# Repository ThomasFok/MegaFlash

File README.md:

# MegaFlash for Apple IIc/IIc+

MegaFlash is an internal storage device for Apple IIc/IIc plus computer.

## Feature List

- 128MB/256MB Capacity, divided into 4/8 ProDOS Drives
- 400kB RAM Disk
- ROM Disk for Disaster Recovery
- 256kB Slinky Emulation on stock firmware
- Boot Menu (Similar to ROM4X/5X)
- Control Panel
- Real Time Clock with ProDOS clock driver
- Network Time Sync (NTP Client)
- Upload/Download ProDOS Image file via WIFI and TFTP Server
- Upload/Download ProDOS Image file via XModem and USB serial port
- FPU for Applesoft BASIC
- Bug fixes of System ROM and Applesoft

A brief [user guide](/userguide.pdf) is available for more information.

## Requirement
- Apple IIc computer with Memory Expansion Card connector or
- Apple IIc plus computer

System ROM replacement is required for MegaFlash to function.

## Hardware
The hardware is quite simple.  All the heavy work is handled by Pi Pico.  Apple 65C02 CPU only needs to copy data between RAM and Pico. Schematic is available [here](./kicad/rev1.0a/schematic-rev1.0a.pdf).

- Raspberry Pi Pico2 W
- Winbond 25Q01 NOR Flash memory
- GAL16V8 PLD for address decode
- 5V to 3.3V Logic Level Shifter

## Project Directories

There are 3 software projects. There is not enough space in Apple ROM to store the Control Panel program.  The program is stored in Pico flash memory. 

`firmware` Project Directory of Apple ROM Patches\
`cpanel` Control Panel project\
`pico` Raspberry Pi Pico firmware\
`common` Common header files used by all 3 projects

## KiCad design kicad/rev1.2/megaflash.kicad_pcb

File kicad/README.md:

# MegaFlash PCB

Currently, there are three PCB revisions, 1.0A, 1.1B and 1.2. They are functionally identical. 

Rev 1.0A board is more compact. It is optimized for machine assembly. 

Rev 1.1B board is bigger. It is designed for hand assembly.  The components are either through hole or 1.27mm pitch SOICs. The picture below is Rev 1.1A PCB. The positions of the flash chips and mounting hole are slightly different on Rev 1.1B PCB.

Rev 1.2 board replaces the GAL16V8 PLD with three 74HC138.

A brief [PCB Assembly Notes](./pcbassemblynotes.pdf) is available for more information.

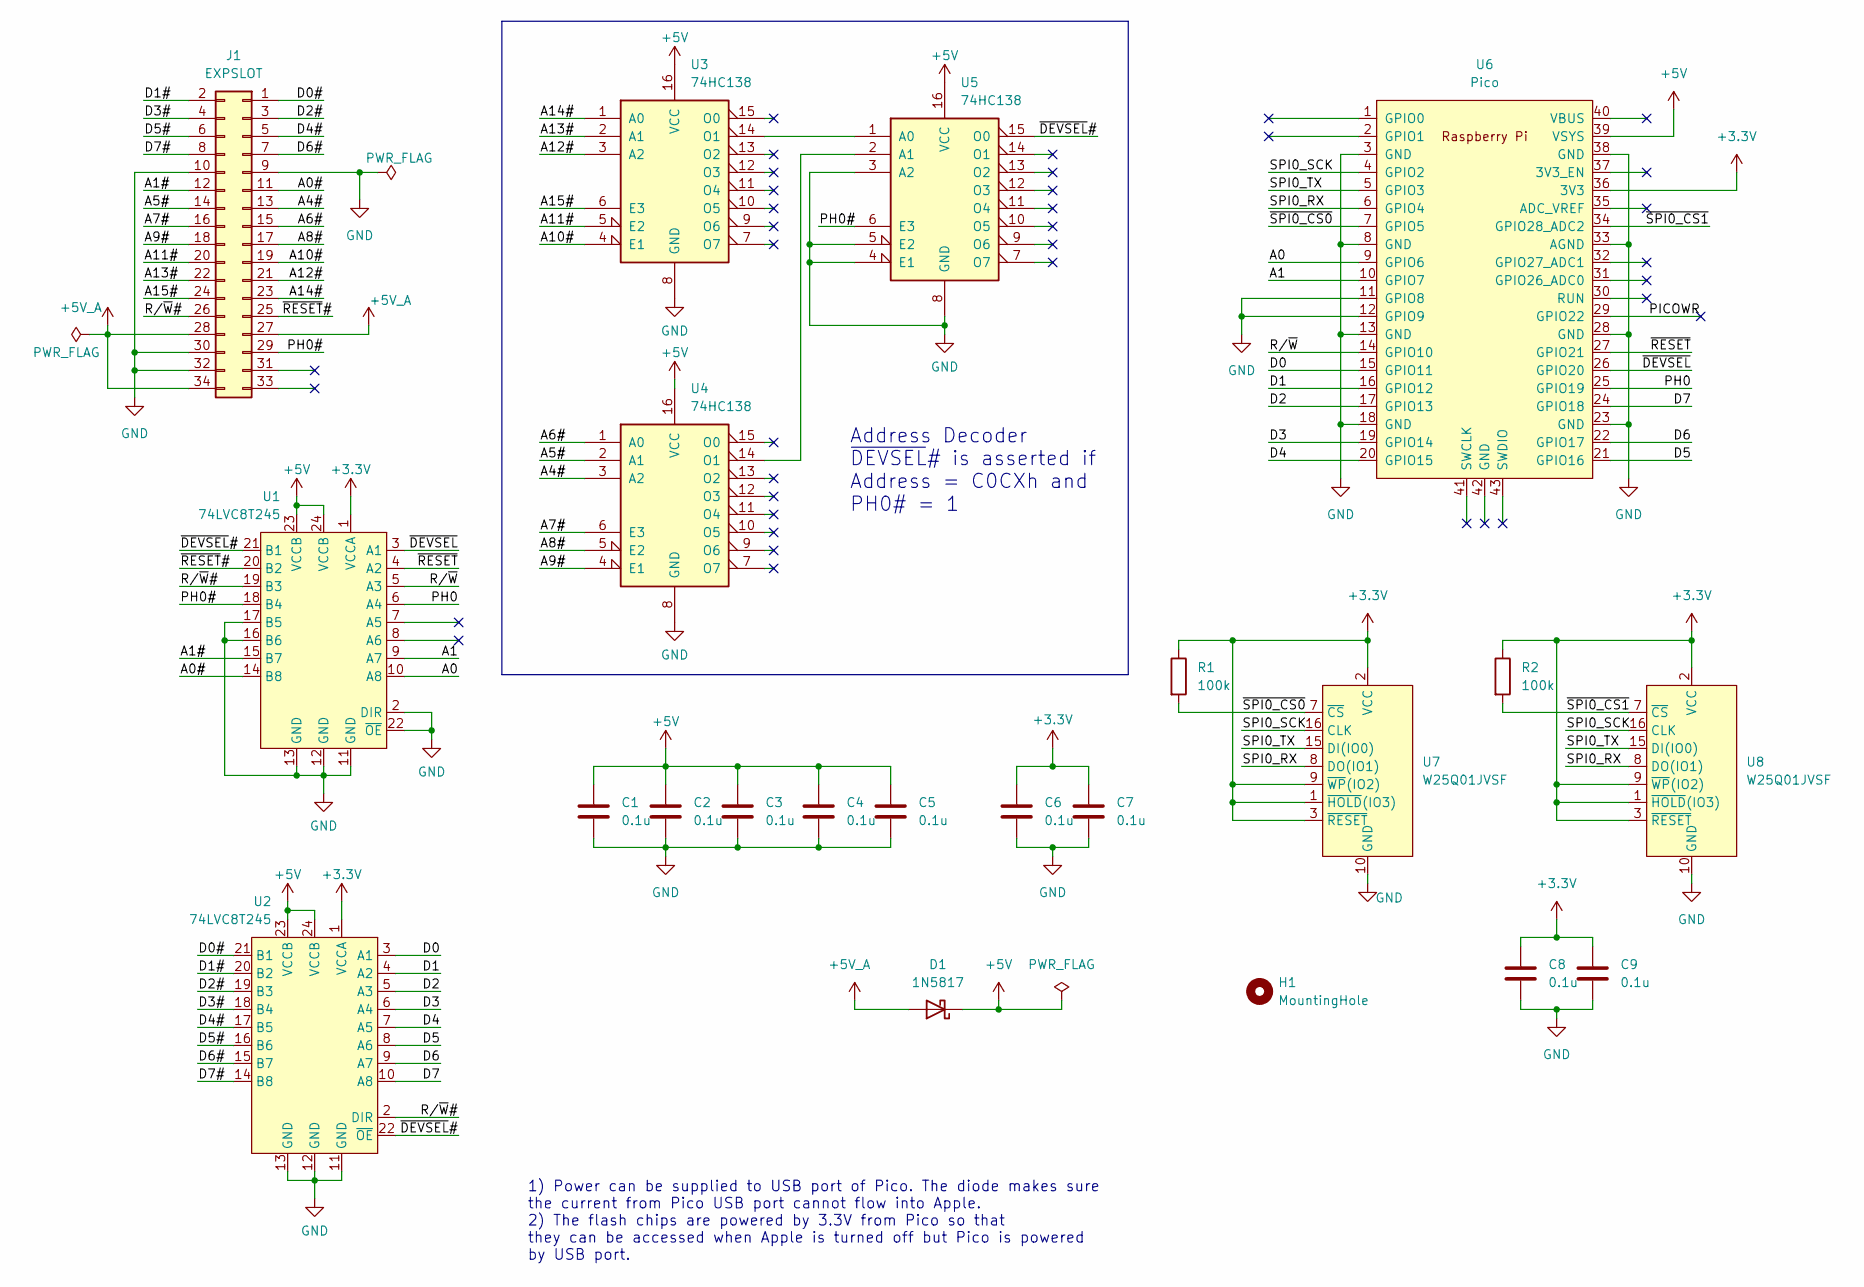
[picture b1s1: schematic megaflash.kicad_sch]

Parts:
C1, C2, C3, C4, C5, C6, C7, C8, C9: 0.1u; C_Disc_D5.1mm_W3.2mm_P5.00mm; Mouser Part No 594-K104K15X7RF5WH5
D1: 1N5817; D_DO-41_SOD81_P10.16mm_Horizontal; Mouser Part No 625-1N5817-E3/53
H1: MountingHole; MountingHole_2.7mm_M2.5
J1: EXPSLOT; PinHeader_2x17_P2.54mm_Vertical_Mirror; Mouser Part No 200-TSW11715GD
R1, R2: 100k; R_Axial_DIN0207_L6.3mm_D2.5mm_P10.16mm_Horizontal
U1, U2: 74LVC8T245; SOIC-24W_7.5x15.4mm_P1.27mm; Mfr Part No SN74LVC8T245DWR; Mouser Part No 595-SN74LVC8T245DWR
U3, U4, U5: 74HC138; SOIC-16_3.9x9.9mm_P1.27mm; Mouser Part No 595-SN74HC138QDRG4Q1
U6: Pico; RPi_Pico_SMD_NO_LABEL_NO_DEBUG
U7, U8: W25Q01JVSF; SOIC-16W_7.5x10.3mm_P1.27mm; Mouser Part No 454-W25Q01JVSFIM

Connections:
+3.3V: C6.1, C7.1, C8.1, C9.1, R1.1, R2.1, U1.1 (VCCA), U2.1 (VCCA), U6.36 (3V3), U7.1 (~HOLD(IO3)), U7.2 (VCC), U7.3 (~RESET), U7.9 (~WP(IO2)), U8.1 (~HOLD(IO3)), U8.2 (VCC), U8.3 (~RESET), U8.9 (~WP(IO2))
+5V: C1.1, C2.1, C3.1, C4.1, C5.1, D1.1 (K), U1.23 (VCCB), U1.24 (VCCB), U2.23 (VCCB), U2.24 (VCCB), U3.16 (VCC), U4.16 (VCC), U5.16 (VCC), U6.39 (VSYS)
+5V_A: D1.2 (A), J1.27, J1.28, J1.34
/A0: U1.10 (A8), U6.9 (GPIO6)
/A0#: J1.11, U1.14 (B8)
/A1: U1.9 (A7), U6.10 (GPIO7)
/A1#: J1.12, U1.15 (B7)
/A4#: J1.13, U4.3 (A2)
/A5#: J1.14, U4.2 (A1)
/A6#: J1.15, U4.1 (A0)
/A7#: J1.16, U4.6 (E3)
/A8#: J1.17, U4.5 (E2)
/A9#: J1.18, U4.4 (E1)
/A10#: J1.19, U3.4 (E1)
/A11#: J1.20, U3.5 (E2)
/A12#: J1.21, U3.3 (A2)
/A13#: J1.22, U3.2 (A1)
/A14#: J1.23, U3.1 (A0)
/A15#: J1.24, U3.6 (E3)
/D0: U2.3 (A1), U6.15 (GPIO11)
/D0#: J1.1, U2.21 (B1)
/D1: U2.4 (A2), U6.16 (GPIO12)
/D1#: J1.2, U2.20 (B2)
/D2: U2.5 (A3), U6.17 (GPIO13)
/D2#: J1.3, U2.19 (B3)
/D3: U2.6 (A4), U6.19 (GPIO14)
/D3#: J1.4, U2.18 (B4)
/D4: U2.7 (A5), U6.20 (GPIO15)
/D4#: J1.5, U2.17 (B5)
/D5: U2.8 (A6), U6.21 (GPIO16)
/D5#: J1.6, U2.16 (B6)
/D6: U2.9 (A7), U6.22 (GPIO17)
/D6#: J1.7, U2.15 (B7)
/D7: U2.10 (A8), U6.24 (GPIO18)
/D7#: J1.8, U2.14 (B8)
/PH0: U1.6 (A4), U6.25 (GPIO19)
/PH0#: J1.29, U1.18 (B4), U5.6 (E3)
/PICOWR: U6.29 (GPIO22)
/R/~W: U1.5 (A3), U6.14 (GPIO10)
/R/~W#: J1.26, U1.19 (B3), U2.2 (DIR)
/SPI0_RX: U6.6 (GPIO4), U7.8 (DO(IO1)), U8.8 (DO(IO1))
/SPI0_SCK: U6.4 (GPIO2), U7.16 (CLK), U8.16 (CLK)
/SPI0_TX: U6.5 (GPIO3), U7.15 (DI(IO0)), U8.15 (DI(IO0))
/~DEVSEL: U1.3 (A1), U6.26 (GPIO20)
/~DEVSEL#: U1.21 (B1), U2.22 (~OE), U5.15 (O0)
/~RESET: U1.4 (A2), U6.27 (GPIO21)
/~RESET#: J1.25, U1.20 (B2)
/~SPI0_CS0: R1.2, U6.7 (GPIO5), U7.7 (~CS)
/~SPI0_CS1: R2.2, U6.34 (GPIO28_ADC2), U8.7 (~CS)
GND: C1.2, C2.2, C3.2, C4.2, C5.2, C6.2, C7.2, C8.2, C9.2, J1.9, J1.10, J1.30, J1.32, U1.2 (DIR), U1.11 (GND), U1.12 (GND), U1.13 (GND), U1.16 (B6), U1.17 (B5), U1.22 (~OE), U2.11 (GND), U2.12 (GND), U2.13 (GND), U3.8 (GND), U4.8 (GND), U5.3 (A2), U5.4 (E1), U5.5 (E2), U5.8 (GND), U6.3 (GND), U6.8 (GND), U6.11 (GPIO8), U6.12 (GPIO9), U6.13 (GND), U6.18 (GND), U6.23 (GND), U6.28 (GND), U6.33 (AGND), U6.38 (GND), U7.10 (GND), U8.10 (GND)
unnamed: U3.14 (O1), U5.1 (A0)
unnamed: U4.14 (O1), U5.2 (A1)

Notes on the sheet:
Address Decoder ~{DEVSEL}# is asserted if Address = C0CXh and PH0# = 1
1) Power can be supplied to USB port of Pico. The diode makes sure the current from Pico USB port cannot flow into Apple. 2) The flash chips are powered by 3.3V from Pico so that they can be accessed when Apple is turned off but Pico is powered by USB port.

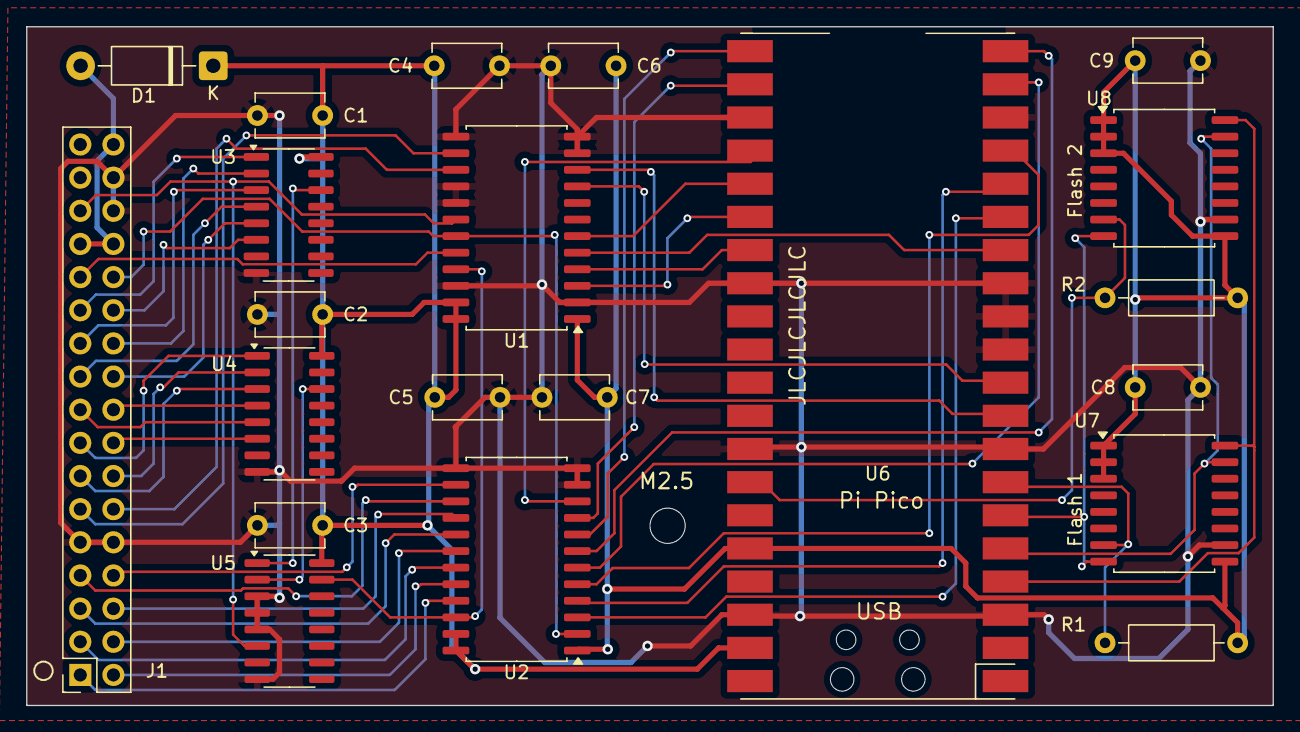
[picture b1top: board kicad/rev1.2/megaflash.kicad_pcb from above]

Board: 2 copper layers, 95.5 x 52.0 mm, 22 parts (0 on the bottom side), 51 nets.

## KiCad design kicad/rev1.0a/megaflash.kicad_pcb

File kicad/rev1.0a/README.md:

### Differences between Rev 1.0A and 1.0 PCB

- The 3.3V voltage regulator is removed. The bus transceiver is powered by Pico board.
- GPIO 8 and 9 of Pico (reserved for A2 and A3 address lines) are grounded.
- The shape of the board is rectangular.

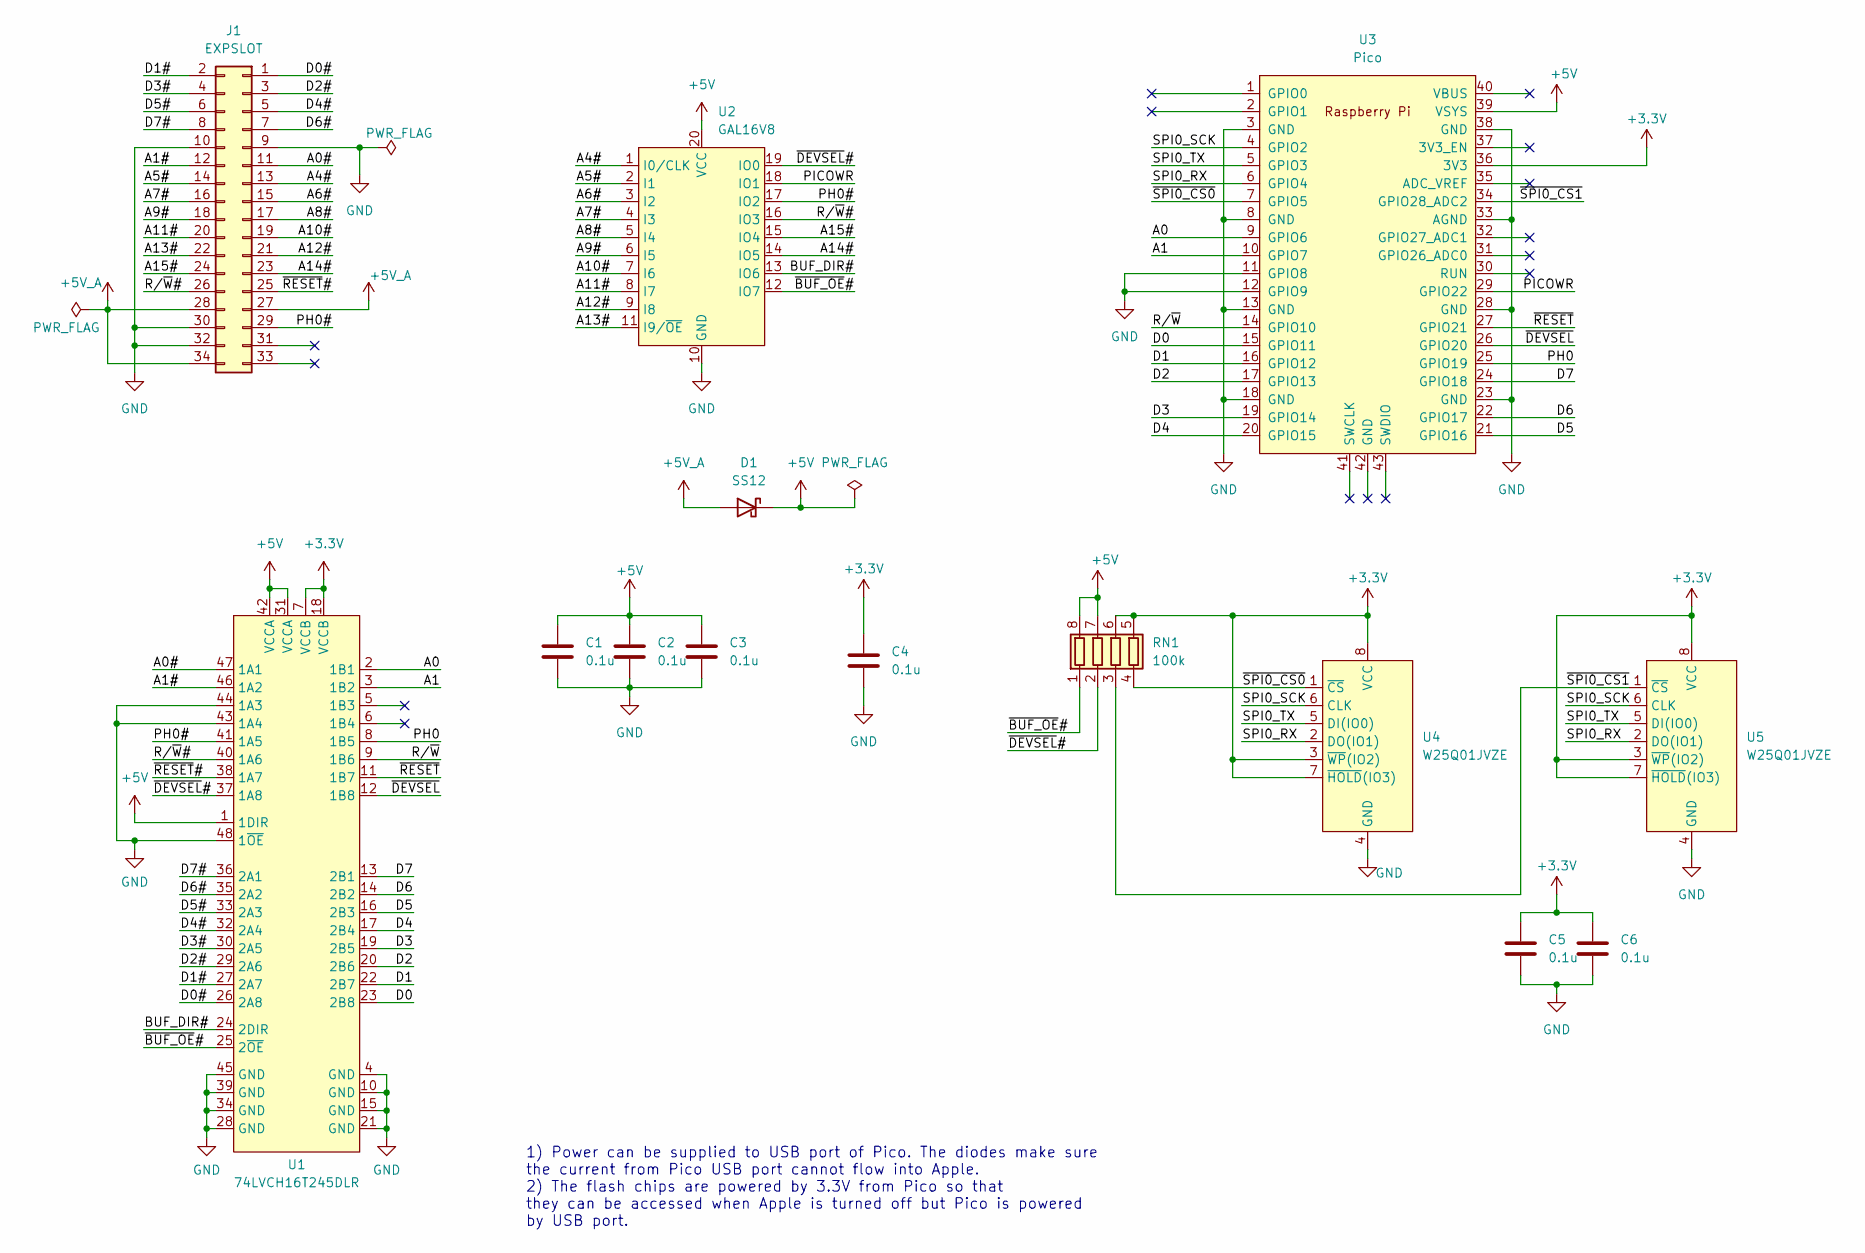
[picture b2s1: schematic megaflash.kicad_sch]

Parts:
C1, C2, C3, C4, C5, C6: 0.1u; C_0805_2012Metric_Pad1.18x1.45mm_HandSolder; Mouser Part No 80-C0805C104M5R
D1: SS12; D_SMA; Mouser Part No 625-SS12-E3
J1: EXPSLOT; PinHeader_2x17_P2.54mm_Vertical_Mirror; Mouser Part No 200-TSW11715GD
RN1: 100k; R_Array_Convex_4x0603; Mouser Part No 667-EXB-V8V104JV
U1: 74LVCH16T245DLR; SSOP-48_7.5x15.9mm_P0.635mm; Mouser Part No 595-SN74LVCH16T245LR
U2: GAL16V8; PLCC-20_SMD-Socket
U3: Pico; RPi_Pico_SMD_NO_LABEL_NO_DEBUG
U4, U5: W25Q01JVZE; WSON-8-1EP_8x6mm_P1.27mm_EP3.4x4.3mm; Mouser Part No 454-W25Q01JVZEIMTU

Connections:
+3.3V: C4.1, C5.1, C6.1, RN1.5 (R4.2), RN1.6 (R3.2), U1.7 (VCCB), U1.18 (VCCB), U3.36 (3V3), U4.3 (~WP(IO2)), U4.7 (~HOLD(IO3)), U4.8 (VCC), U5.3 (~WP(IO2)), U5.7 (~HOLD(IO3)), U5.8 (VCC)
+5V: C1.1, C2.1, C3.1, D1.1 (K), RN1.7 (R2.2), RN1.8 (R1.2), U1.1 (1DIR), U1.31 (VCCA), U1.42 (VCCA), U2.20 (VCC), U3.39 (VSYS)
+5V_A: D1.2 (A), J1.27, J1.28, J1.34
/A0: U1.2 (1B1), U3.9 (GPIO6)
/A0#: J1.11, U1.47 (1A1)
/A1: U1.3 (1B2), U3.10 (GPIO7)
/A1#: J1.12, U1.46 (1A2)
/A4#: J1.13, U2.1 (I0/CLK)
/A5#: J1.14, U2.2 (I1)
/A6#: J1.15, U2.3 (I2)
/A7#: J1.16, U2.4 (I3)
/A8#: J1.17, U2.5 (I4)
/A9#: J1.18, U2.6 (I5)
/A10#: J1.19, U2.7 (I6)
/A11#: J1.20, U2.8 (I7)
/A12#: J1.21, U2.9 (I8)
/A13#: J1.22, U2.11 (I9/~OE)
/A14#: J1.23, U2.14 (IO5)
/A15#: J1.24, U2.15 (IO4)
/BUF_DIR#: U1.24 (2DIR), U2.13 (IO6)
/D0: U1.23 (2B8), U3.15 (GPIO11)
/D0#: J1.1, U1.26 (2A8)
/D1: U1.22 (2B7), U3.16 (GPIO12)
/D1#: J1.2, U1.27 (2A7)
/D2: U1.20 (2B6), U3.17 (GPIO13)
/D2#: J1.3, U1.29 (2A6)
/D3: U1.19 (2B5), U3.19 (GPIO14)
/D3#: J1.4, U1.30 (2A5)
/D4: U1.17 (2B4), U3.20 (GPIO15)
/D4#: J1.5, U1.32 (2A4)
/D5: U1.16 (2B3), U3.21 (GPIO16)
/D5#: J1.6, U1.33 (2A3)
/D6: U1.14 (2B2), U3.22 (GPIO17)
/D6#: J1.7, U1.35 (2A2)
/D7: U1.13 (2B1), U3.24 (GPIO18)
/D7#: J1.8, U1.36 (2A1)
/PH0: U1.8 (1B5), U3.25 (GPIO19)
/PH0#: J1.29, U1.41 (1A5), U2.17 (IO2)
/PICOWR: U2.18 (IO1), U3.29 (GPIO22)
/R/~W: U1.9 (1B6), U3.14 (GPIO10)
/R/~W#: J1.26, U1.40 (1A6), U2.16 (IO3)
/SPI0_RX: U3.6 (GPIO4), U4.2 (DO(IO1)), U5.2 (DO(IO1))
/SPI0_SCK: U3.4 (GPIO2), U4.6 (CLK), U5.6 (CLK)
/SPI0_TX: U3.5 (GPIO3), U4.5 (DI(IO0)), U5.5 (DI(IO0))
/~BUF_OE#: RN1.1 (R1.1), U1.25 (2~OE), U2.12 (IO7)
/~DEVSEL: U1.12 (1B8), U3.26 (GPIO20)
/~DEVSEL#: RN1.2 (R2.1), U1.37 (1A8), U2.19 (IO0)
/~RESET: U1.11 (1B7), U3.27 (GPIO21)
/~RESET#: J1.25, U1.38 (1A7)
/~SPI0_CS0: RN1.4 (R4.1), U3.7 (GPIO5), U4.1 (~CS)
/~SPI0_CS1: RN1.3 (R3.1), U3.34 (GPIO28_ADC2), U5.1 (~CS)
GND: C1.2, C2.2, C3.2, C4.2, C5.2, C6.2, J1.9, J1.10, J1.30, J1.32, U1.4 (GND), U1.10 (GND), U1.15 (GND), U1.21 (GND), U1.28 (GND), U1.34 (GND), U1.39 (GND), U1.43 (1A4), U1.44 (1A3), U1.45 (GND), U1.48 (1~OE), U2.10 (GND), U3.3 (GND), U3.8 (GND), U3.11 (GPIO8), U3.12 (GPIO9), U3.13 (GND), U3.18 (GND), U3.23 (GND), U3.28 (GND), U3.33 (AGND), U3.38 (GND), U4.4 (GND), U5.4 (GND)

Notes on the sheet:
1) Power can be supplied to USB port of Pico. The diodes make sure the current from Pico USB port cannot flow into Apple. 2) The flash chips are powered by 3.3V from Pico so that they can be accessed when Apple is turned off but Pico is powered by USB port.

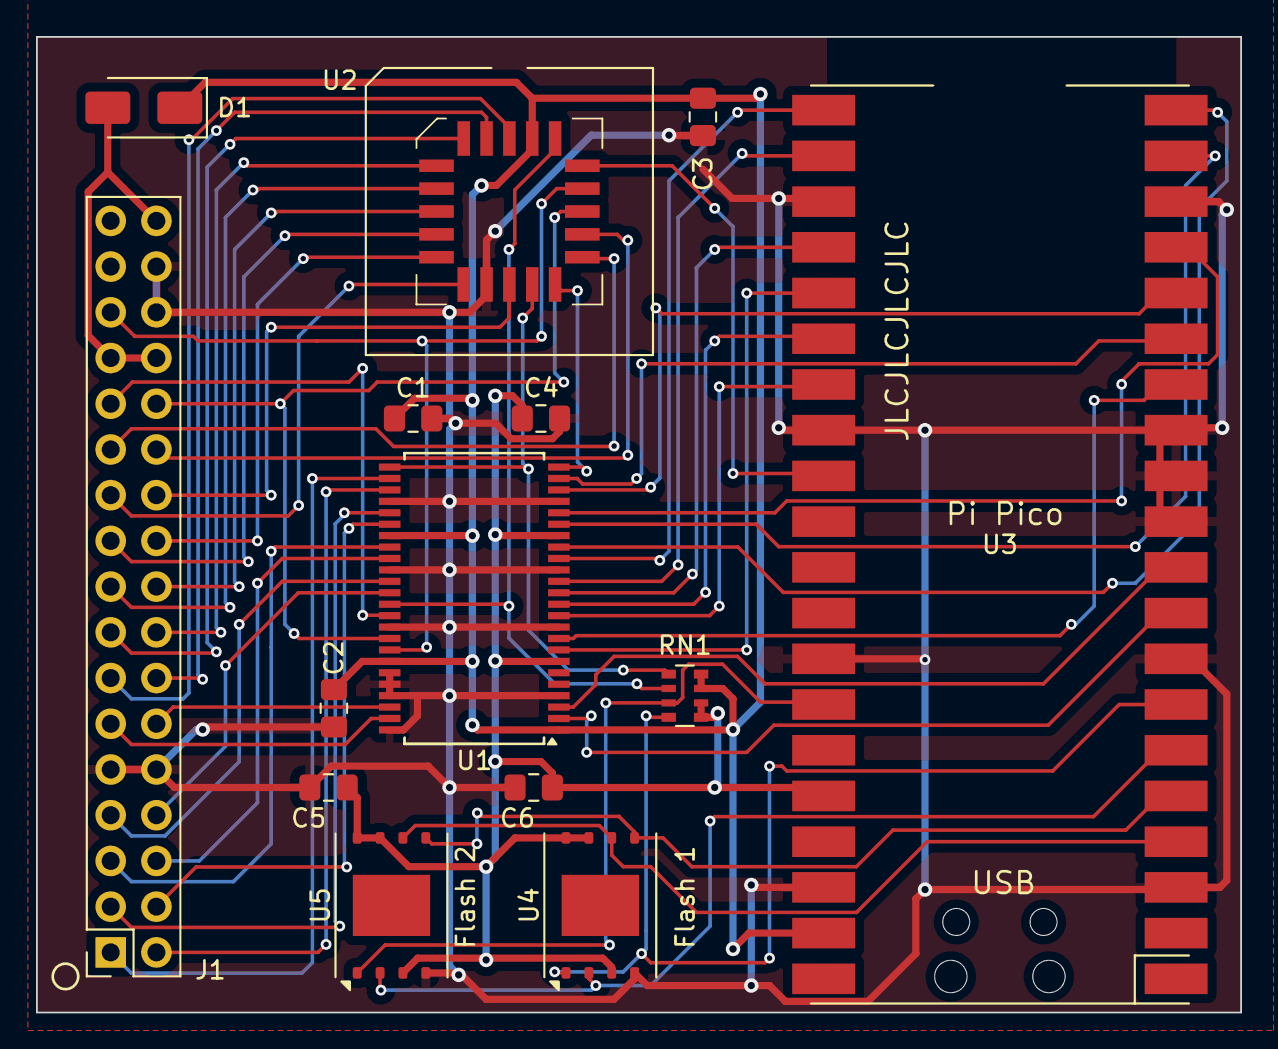
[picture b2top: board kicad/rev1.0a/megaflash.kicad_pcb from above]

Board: 2 copper layers, 66.9 x 54.2 mm, 14 parts (0 on the bottom side), 52 nets.

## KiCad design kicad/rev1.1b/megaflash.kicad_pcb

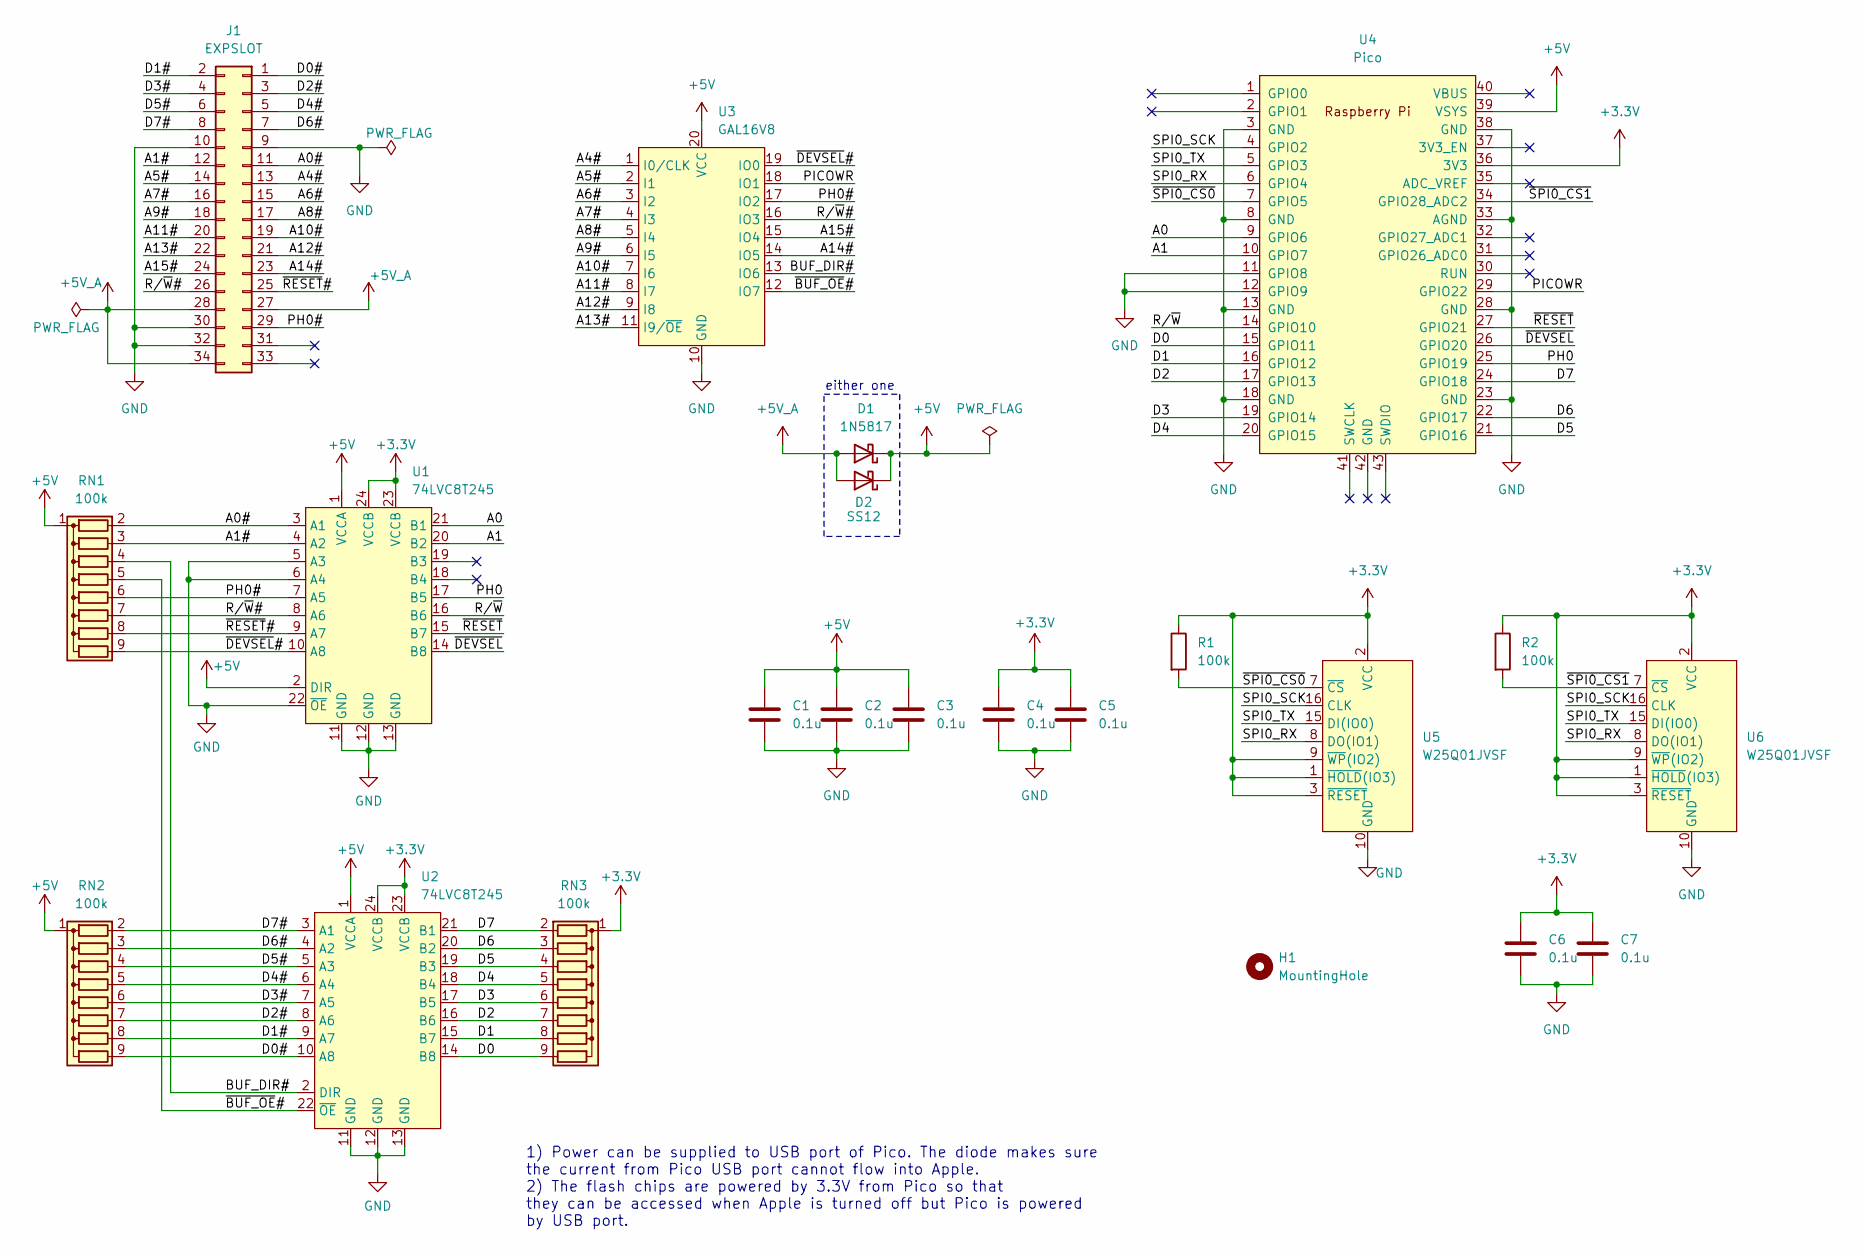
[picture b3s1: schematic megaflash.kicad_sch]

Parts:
C1, C2, C3, C4, C5, C6, C7: 0.1u; C_Disc_D5.1mm_W3.2mm_P5.00mm; Mouser Part No 594-K104K15X7RF5WH5
D1: 1N5817; D_DO-41_SOD81_P10.16mm_Horizontal; Mouser Part No 625-1N5817-E3/53
D2: SS12; D_SMA; Mouser Part No 625-SS12-E3
H1: MountingHole; MountingHole_2.7mm_M2.5
J1: EXPSLOT; PinHeader_2x17_P2.54mm_Vertical_Mirror; Mouser Part No 200-TSW11715GD
R1, R2: 100k; R_Axial_DIN0207_L6.3mm_D2.5mm_P10.16mm_Horizontal
RN1, RN2, RN3: 100k; R_Array_SIP9; Mouser Part No 652-4609X-1LF-100K
U1, U2: 74LVC8T245; SOIC-24W_7.5x15.4mm_P1.27mm; Mfr Part No SN74LVC8T245DWR; Mouser Part No 595-SN74LVC8T245DWR
U3: GAL16V8; DIP-20_W7.62mm_LongPads
U4: Pico; RPi_Pico_SMD_NO_LABEL_NO_DEBUG
U5, U6: W25Q01JVSF; SOIC-16W_7.5x10.3mm_P1.27mm; Mouser Part No 454-W25Q01JVSFIM

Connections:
+3.3V: C4.1, C5.1, C6.1, C7.1, R1.1, R2.1, RN3.1 (common), U1.23 (VCCB), U1.24 (VCCB), U2.23 (VCCB), U2.24 (VCCB), U4.36 (3V3), U5.1 (~HOLD(IO3)), U5.2 (VCC), U5.3 (~RESET), U5.9 (~WP(IO2)), U6.1 (~HOLD(IO3)), U6.2 (VCC), U6.3 (~RESET), U6.9 (~WP(IO2))
+5V: C1.1, C2.1, C3.1, D1.1 (K), D2.1 (K), RN1.1 (common), RN2.1 (common), U1.1 (VCCA), U1.2 (DIR), U2.1 (VCCA), U3.20 (VCC), U4.39 (VSYS)
+5V_A: D1.2 (A), D2.2 (A), J1.27, J1.28, J1.34
/A0: U1.21 (B1), U4.9 (GPIO6)
/A0#: J1.11, RN1.2 (R1), U1.3 (A1)
/A1: U1.20 (B2), U4.10 (GPIO7)
/A1#: J1.12, RN1.3 (R2), U1.4 (A2)
/A4#: J1.13, U3.1 (I0/CLK)
/A5#: J1.14, U3.2 (I1)
/A6#: J1.15, U3.3 (I2)
/A7#: J1.16, U3.4 (I3)
/A8#: J1.17, U3.5 (I4)
/A9#: J1.18, U3.6 (I5)
/A10#: J1.19, U3.7 (I6)
/A11#: J1.20, U3.8 (I7)
/A12#: J1.21, U3.9 (I8)
/A13#: J1.22, U3.11 (I9/~OE)
/A14#: J1.23, U3.14 (IO5)
/A15#: J1.24, U3.15 (IO4)
/BUF_DIR#: RN1.4 (R3), U2.2 (DIR), U3.13 (IO6)
/D0: RN3.9 (R8), U2.14 (B8), U4.15 (GPIO11)
/D0#: J1.1, RN2.9 (R8), U2.10 (A8)
/D1: RN3.8 (R7), U2.15 (B7), U4.16 (GPIO12)
/D1#: J1.2, RN2.8 (R7), U2.9 (A7)
/D2: RN3.7 (R6), U2.16 (B6), U4.17 (GPIO13)
/D2#: J1.3, RN2.7 (R6), U2.8 (A6)
/D3: RN3.6 (R5), U2.17 (B5), U4.19 (GPIO14)
/D3#: J1.4, RN2.6 (R5), U2.7 (A5)
/D4: RN3.5 (R4), U2.18 (B4), U4.20 (GPIO15)
/D4#: J1.5, RN2.5 (R4), U2.6 (A4)
/D5: RN3.4 (R3), U2.19 (B3), U4.21 (GPIO16)
/D5#: J1.6, RN2.4 (R3), U2.5 (A3)
/D6: RN3.3 (R2), U2.20 (B2), U4.22 (GPIO17)
/D6#: J1.7, RN2.3 (R2), U2.4 (A2)
/D7: RN3.2 (R1), U2.21 (B1), U4.24 (GPIO18)
/D7#: J1.8, RN2.2 (R1), U2.3 (A1)
/PH0: U1.17 (B5), U4.25 (GPIO19)
/PH0#: J1.29, RN1.6 (R5), U1.7 (A5), U3.17 (IO2)
/PICOWR: U3.18 (IO1), U4.29 (GPIO22)
/R/~W: U1.16 (B6), U4.14 (GPIO10)
/R/~W#: J1.26, RN1.7 (R6), U1.8 (A6), U3.16 (IO3)
/SPI0_RX: U4.6 (GPIO4), U5.8 (DO(IO1)), U6.8 (DO(IO1))
/SPI0_SCK: U4.4 (GPIO2), U5.16 (CLK), U6.16 (CLK)
/SPI0_TX: U4.5 (GPIO3), U5.15 (DI(IO0)), U6.15 (DI(IO0))
/~BUF_OE#: RN1.5 (R4), U2.22 (~OE), U3.12 (IO7)
/~DEVSEL: U1.14 (B8), U4.26 (GPIO20)
/~DEVSEL#: RN1.9 (R8), U1.10 (A8), U3.19 (IO0)
/~RESET: U1.15 (B7), U4.27 (GPIO21)
/~RESET#: J1.25, RN1.8 (R7), U1.9 (A7)
/~SPI0_CS0: R1.2, U4.7 (GPIO5), U5.7 (~CS)
/~SPI0_CS1: R2.2, U4.34 (GPIO28_ADC2), U6.7 (~CS)
GND: C1.2, C2.2, C3.2, C4.2, C5.2, C6.2, C7.2, J1.9, J1.10, J1.30, J1.32, U1.5 (A3), U1.6 (A4), U1.11 (GND), U1.12 (GND), U1.13 (GND), U1.22 (~OE), U2.11 (GND), U2.12 (GND), U2.13 (GND), U3.10 (GND), U4.3 (GND), U4.8 (GND), U4.11 (GPIO8), U4.12 (GPIO9), U4.13 (GND), U4.18 (GND), U4.23 (GND), U4.28 (GND), U4.33 (AGND), U4.38 (GND), U5.10 (GND), U6.10 (GND)

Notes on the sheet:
1) Power can be supplied to USB port of Pico. The diode makes sure the current from Pico USB port cannot flow into Apple. 2) The flash chips are powered by 3.3V from Pico so that they can be accessed when Apple is turned off but Pico is powered by USB port.
either one

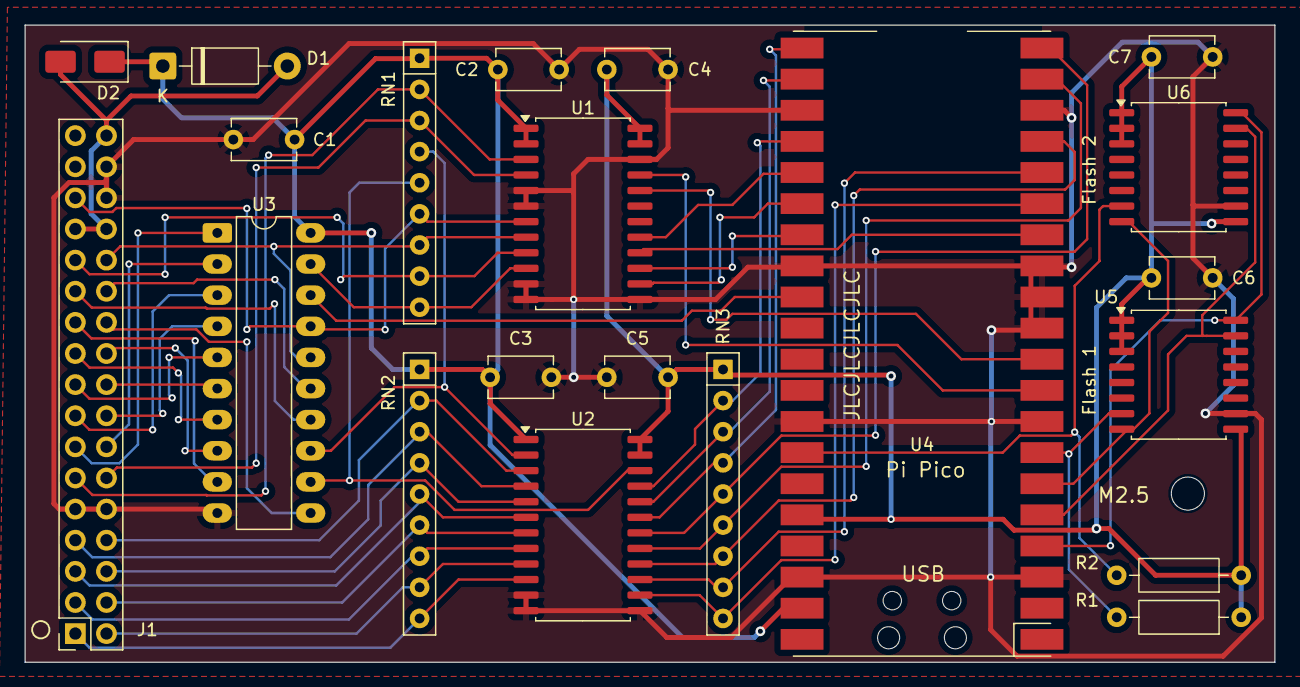
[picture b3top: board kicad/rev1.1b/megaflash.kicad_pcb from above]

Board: 2 copper layers, 102.0 x 52.0 mm, 22 parts (0 on the bottom side), 52 nets.

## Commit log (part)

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2025-09-05 PCB Rev 1.1A images
2025-09-05 Remove rev1.1 PCB
2025-09-05 Added Rev1.1A PCB
2025-09-05 Corrected filename
2025-09-05 Removed Rev1.1a PCB
2025-09-05 Rev 1.1b PCB
2025-09-05 Revised Rev1.1b PCB
2025-09-06 Revised PCB Rev 1.1B
2025-09-07 Rev 1.0A PCB
2025-09-07 Rev 1.0A image
2025-09-07 Updated schematic
2025-09-10 Optimized the timing of RP2350 pio
2025-09-10 Ver 1.1.6
2025-09-13 Added PCB Assembly Notes
2025-09-18 Updated comment
2025-09-18 Removed disabled code
2025-09-18 Refactor flash access routines to hide implementation details
2025-09-19 Mutex Lock in exported functions only
2025-09-19 Removed DMA usage from romdisk.c
2025-09-19 Ramdisk has its own dedicated DMA channel
2025-09-19 Removed unnecessary DMA access
2025-09-19 Reduced memory usage
2025-09-19 Show heap usage in Device Information
2025-09-20 Updated user guide
2025-09-20 Updated prompt messages
2025-09-20 Version 1.1.7
2025-09-20 Updated comments
2025-09-20 Corrected comments
2026-02-02 Corrected typo
2026-02-06 Corrected comment
2026-02-06 Corrected code formatting
2026-02-20 Code Cleanup
2026-02-21 Removed unused constants
2026-02-21 Corrected typos and code clean up
2026-02-21 Added static keyword
2026-02-21 Added status keyword
2026-02-22 Updated userguide.pdf
2026-02-22 Added comment about SPI mode
2026-02-22 Reduced memory usage in SLOTROM segment
2026-02-22 jmp to boot menu via swjmp routine
2026-02-22 Updated version.txt
2026-02-22 Optimized data transfer routines
2026-02-22 Saved 3 bytes of ROM space
2026-02-23 Centre the title string
2026-02-24 Optimized the speed of data transfer routine
2026-02-24 Updated loadcpanel routine
2026-02-24 Changed firmware version to 1.0.1
2026-02-24 Minor code change
2026-02-24 Moved dispatch routine to ROM1 segment
2026-02-24 Removed unused code
2026-02-24 Updated .gitignore
2026-02-24 Optimized p8spentry routine
2026-02-24 Replaced > and < operators with .HIBYTE and .LOBYTE
2026-02-24 Updted comment
2026-02-24 Partially unroll data transfer loops
2026-02-25 Made use of free space in - of Aux ROM bank
2026-02-25 Rearranged segment allocation
2026-02-25 Moved getdib from IOROM to ROM1 segment
2026-02-25 Updated speed test results
2026-02-26 Corrected the description of SPI mode
2026-02-27 Changed void* to proper type
2026-02-27 Added CMD_FSUB command
2026-02-27 Renamed variable
2026-03-01 Auto adjust PIO clock divider from clk_sys
2026-03-01 Changed prompt message
2026-03-01 Clean up slinky.c source code
2026-03-02 Source code cleanup
2026-03-02 Added comment on RX DMA Channel
2026-03-02 Removed IRQ0 from RP2350 pio
2026-03-03 Renamed Timer commands to Stopwatch
2026-03-03 Adjusted loop count from clk_sys
2026-03-03 Added OverclockCPU() function
2026-03-03 Removed unused #include
2026-03-03 Removed __no_inline_not_in_flash_func from some functions
2026-03-04 Moved all functions to flash memory
2026-03-04 Applied inline selectively
2026-03-04 Moved definition of union registers from a2bus.c to busloop.c
2026-03-04 Source code clean up
2026-03-05 Optimized DMA routines
2026-03-05 Added comment
2026-03-05 Optimized LoadFAC and LoadARG routines
2026-03-06 Bug fix: correct output when d==0
2026-03-06 Optimized StoreResult routine
2026-03-06 Formatting
2026-03-06 StoreResult() writes sign bit to correct location
2026-03-06 Reduced code size
2026-03-06 Reduced sleep duration
2026-03-06 Assigned FPU segment to address
2026-03-06 Unrolled data transfer loop
2026-03-07 Added fswrts routine to improve performance on IIc+
2026-03-07 Added .DS_Store to .gitignore
2026-03-07 Removed unnecessary instruction
2026-03-07 Moved portion of slxeq2 routine to ROM1 for better performance on IIc+
2026-03-07 Enabled CPU overclocking
2026-03-07 Changed version to 1.1.8
2026-03-07 Clean up Makefile
2026-03-08 Set CYW43 PIO clock divider if CPU is overclocked
2026-03-08 Disabled overclock due to unreliablity of WIFI
2026-03-09 Increase core voltage to 1.15V when overclock
2026-03-10 Corrected typos
2026-03-11 Fix: ReadFromFlashByDMA() hangs when CPU is overclocked
2026-03-11 Moved CPU overclock build flag to CMakeLists.txt
2026-03-12 When Esc key is pressed from main menu, ask user to save the settings before exiting
2026-03-14 Fix: NTP is updated twice when power on
2026-03-14 Call EvtUDPReceived() from udp_callback()
2026-03-14 Avoid race condition with TFTP server
2026-03-14 Added delay before wrapping
2026-03-15 Added const keyword
2026-03-15 TFTP Download with DOS order image support
2026-03-15 Changed prompt message for TFTP DO support
2026-03-16 Changed menu position
2026-03-17 Compiled control panel binaries
2026-03-17 Updated for V1.1.9
2026-03-17 Call EvtUDPReceived() from CUDPTask::Run() instead of udp_callback()
2026-03-17 Updated version number
2026-03-17 Added copy constructor and move constructor
2026-03-17 Added cyw43_arch_lwip_begin()/_end()
2026-03-17 Added helper class CInterrupt
2026-03-17 Don't call cyw43_arch_lwip_begin()/_end() if rwpbuf is nullptr
2026-03-17 Renamed udp_callback() to udp_recv_callback()
2026-03-18 Added IsAbortRequested() method
2026-03-18 Renamed method name to ValidateBlockNumber()
2026-03-18 Renamed CInterrupt to CInterruptDisabler
2026-03-19 V1.1.10
2026-03-21 Added static_assert()
2026-03-24 Added CLAMP macro
2026-03-25 Managed task pointer with std::unique_ptr
2026-03-26 Added override keyword
2026-03-26 Discarded the data if blockCount<8
2026-03-27 Device Info shows GCC Version
2026-04-05 Removed excess blank lines
2026-04-05 Text Formatting
2026-04-05 Set C17 and C++17 standard
2026-04-06 Added Alliance AS25F3512MQ flash support
2026-04-25 Replaced std::queue with a ring buffer
2026-04-25 Updated version info
2026-04-25 When 6502 reads status register, the request is not forwared to the CPU.
2026-04-25 Handled word order with macro instead of const
2026-04-26 Fix: TFTP failed to restart when blksize option from server is invalid.
2026-04-26 Text formattting
2026-04-28 Experimental ISSI Flash chip support
2026-05-17 Revision 1.2 PCB
2026-05-18 Pico Firmware V1.1.11
2026-06-11 Fix: ProDOS Driver Status command returned wrong drive capacity.
2026-06-12 Slot number is configurable.
